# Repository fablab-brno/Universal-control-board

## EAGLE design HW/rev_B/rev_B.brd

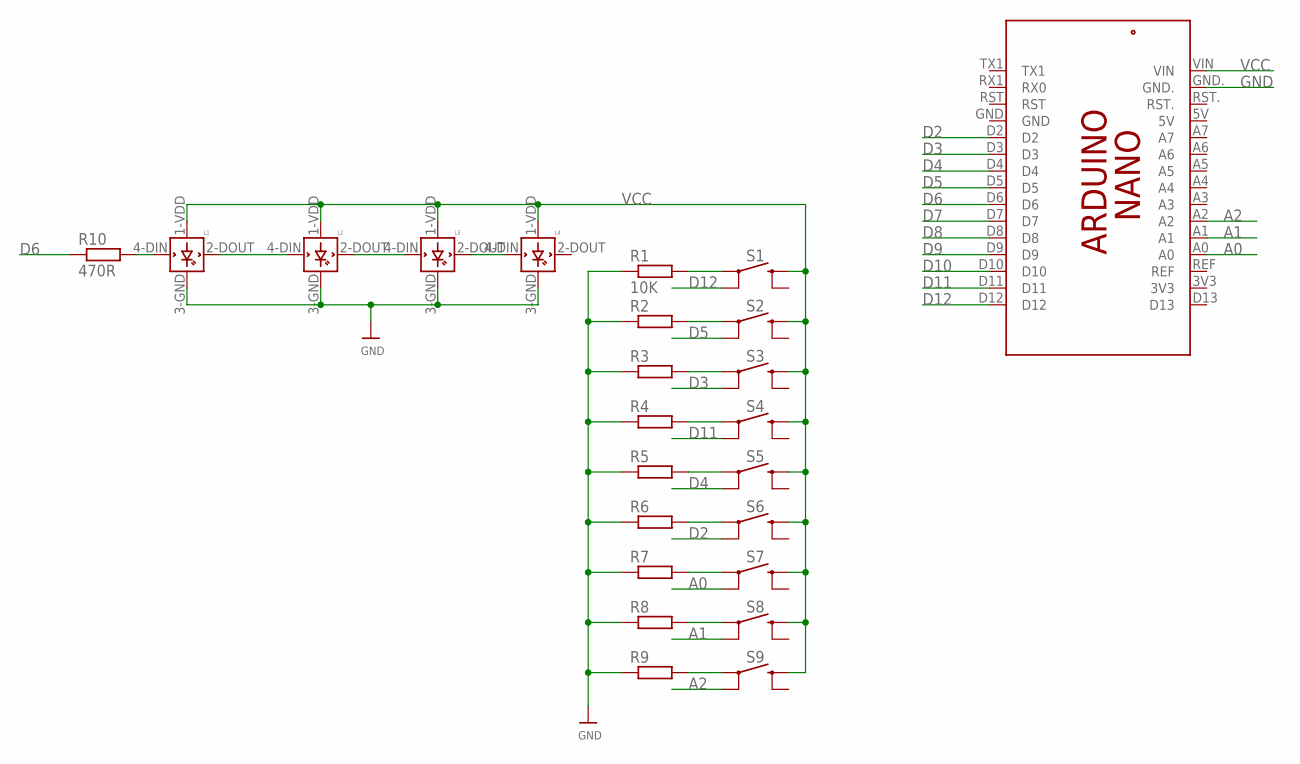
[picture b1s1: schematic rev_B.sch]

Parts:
L1, L2, L3, L4: WS2812B
PCB1: ARDUINO_NANO
R1: 10K; R0805
R2, R3, R4, R5, R6, R7, R8, R9: R-EU_R0805; R0805
R10: 470R; R0805
S1, S2, S3, S4, S5, S6, S7, S8, S9: TACT_SWITCH_12MM

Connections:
A0: PCB1.A0, S7.2 (3)
A1: PCB1.A1, S8.2 (3)
A2: PCB1.A2, S9.2 (3)
D2: PCB1.D2, S6.2 (3)
D3: PCB1.D3, S3.2 (3)
D4: PCB1.D4, S5.2 (3)
D5: PCB1.D5, S2.2 (3)
D6: PCB1.D6, R10.1
D7: PCB1.D7
D8: PCB1.D8
D9: PCB1.D9
D10: PCB1.D10
D11: PCB1.D11, S4.2 (3)
D12: PCB1.D12, S1.2 (3)
GND: L1.3-GND (GND), L2.3-GND (GND), L3.3-GND (GND), L4.3-GND (GND), PCB1.GND., R1.1, R2.1, R3.1, R4.1, R5.1, R6.1, R7.1, R8.1, R9.1
unnamed: R1.2, S1.1
unnamed: L1.4-DIN (DIN), R10.2
unnamed: R9.2, S9.1
unnamed: R8.2, S8.1
unnamed: R7.2, S7.1
unnamed: R6.2, S6.1
unnamed: R5.2, S5.1
unnamed: R4.2, S4.1
unnamed: R3.2, S3.1
unnamed: R2.2, S2.1
unnamed: L1.2-DOUT (DOUT), L2.4-DIN (DIN)
unnamed: L2.2-DOUT (DOUT), L3.4-DIN (DIN)
unnamed: L3.2-DOUT (DOUT), L4.4-DIN (DIN)
VCC: L1.1-VDD (VDD), L2.1-VDD (VDD), L3.1-VDD (VDD), L4.1-VDD (VDD), PCB1.VIN, S1.3 (2), S2.3 (2), S3.3 (2), S4.3 (2), S5.3 (2), S6.3 (2), S7.3 (2), S8.3 (2), S9.3 (2)

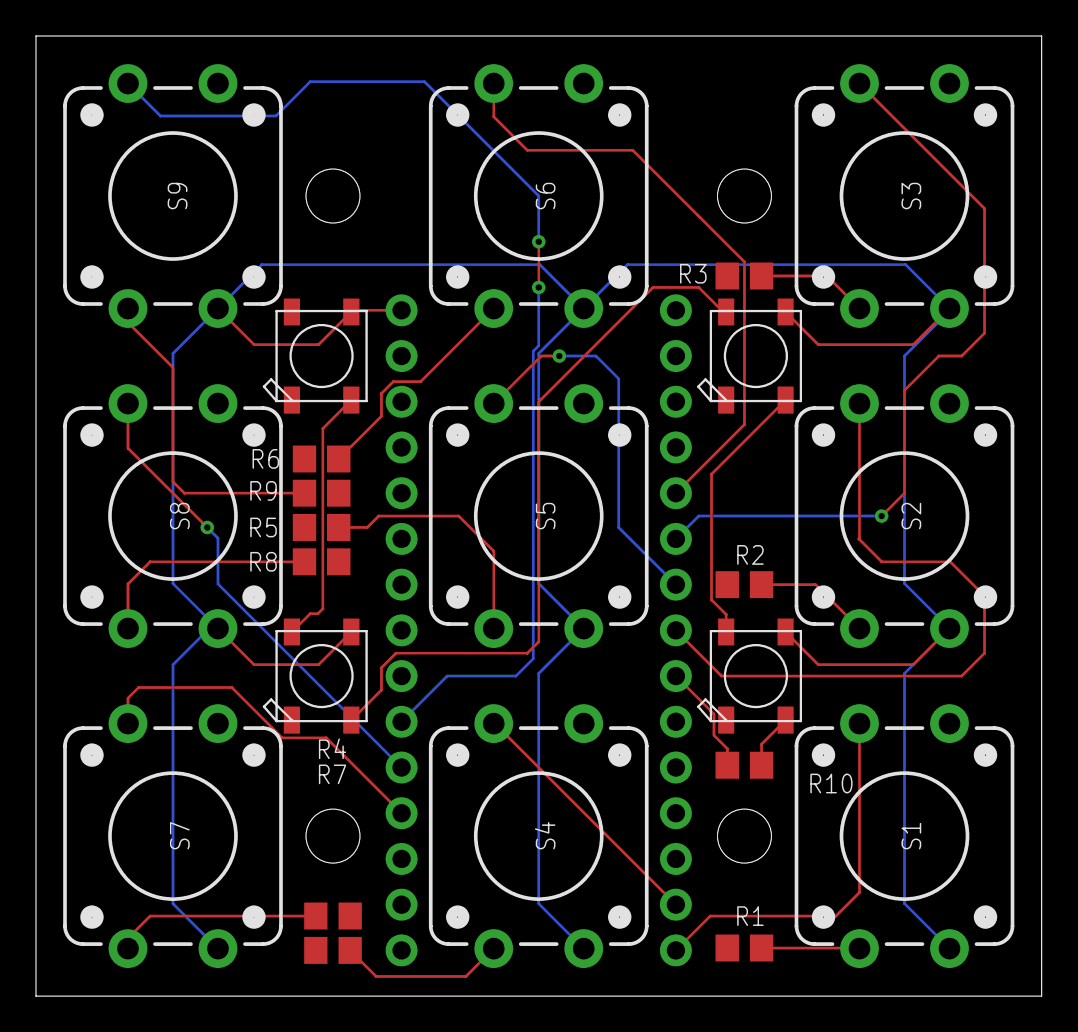
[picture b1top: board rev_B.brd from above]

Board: 2 copper layers, 55.9 x 53.3 mm, 24 parts (1 on the bottom side), 25 nets.

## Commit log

2018-08-09 file upload for rev_B
2018-11-26 Set theme jekyll-theme-cayman

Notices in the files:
parts and their libraries:
microbuilder: This work is placed in the public domain, and may be freely used for commercial and non-commercial work with the following conditions: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
